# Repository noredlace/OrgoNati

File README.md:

# OrgoNati

A design by u/lizardsticks

A an ergonomic ortholinear angled board. Inspiration from the atreus with a twist on the modifiers and keys to fit most keycap designs. <br /> 

Nonstandard keycaps include the 2.25u Novelty on the left side. This keycap is meant to be used with either the Enter Key or a Novelty Enter Key. This allows a symmetrical design.

The left shift key was chosen to be a 2.75u with the right shift being a split shift 1.75u + 1u key.

Schematic was done in a 9 x 8 layout. This is due to the 66 keys on the OrgoNati. Limitations of the ProMicro's PinOuts means the tracing is messy due to the odd path of each switch/diode. <br />

The glory of ugly tracing can be seen

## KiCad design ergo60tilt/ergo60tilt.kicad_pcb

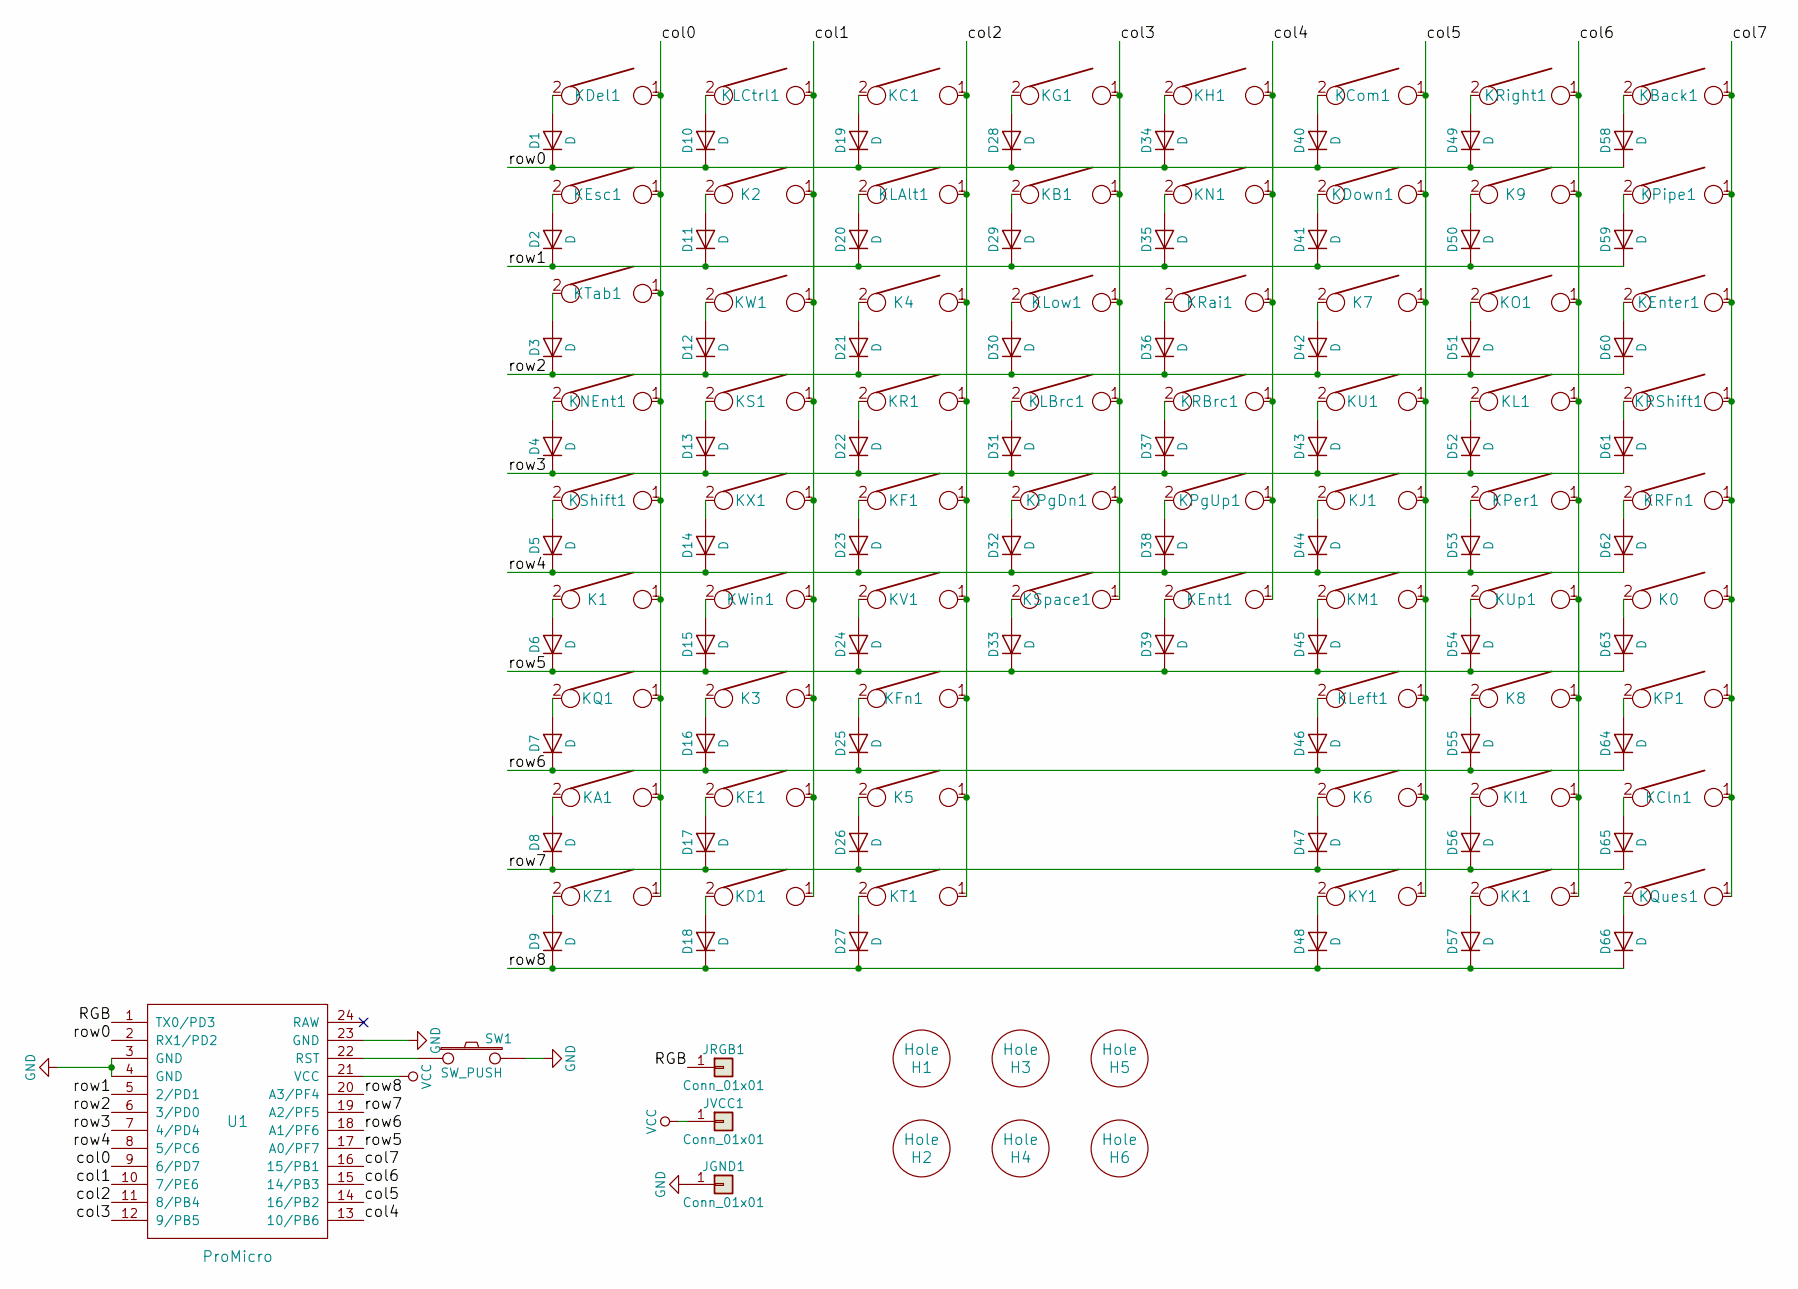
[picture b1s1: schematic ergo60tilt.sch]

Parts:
D1, D2, D3, D4, D5, D6, D7, D8, D9, D10, D11, D12, D13, D14, D15, D16, D17, D18, D19, D20, D21, D22, D23, D24, D25, D26, D27, D28, D29, D30, D31, D32, D33, D34, D35, D36, D37, D38, D39, D40, D41, D42, D43, D44, D45, D46, D47, D48, D49, D50, D51, D52, D53, D54, D55, D56, D57, D58, D59, D60, D61, D62, D63, D64, D65, D66: D; D_SOD123_axial
H1, H2, H3, H4, H5, H6: Hole; HOLE_M2.6
JGND1: Conn_01x01; Pin_d0.9mm_L10.0mm_W2.4mm_FlatFork
JRGB1: Conn_01x01; Pin_d0.9mm_L10.0mm_W2.4mm_FlatFork
JVCC1: Conn_01x01; Pin_d0.9mm_L10.0mm_W2.4mm_FlatFork
K0, K1, K2, K3, K4, K5, K6, K7, K8, K9: KEYSW; Mx_Alps_100
KA1: KEYSW; Mx_Alps_100
KB1: KEYSW; Mx_Alps_100
KBack1: KEYSW; Mx_Alps_200
KC1: KEYSW; Mx_Alps_100
KCln1: KEYSW; Mx_Alps_100
KCom1: KEYSW; Mx_Alps_100
KD1: KEYSW; Mx_Alps_100
KDel1: KEYSW; Mx_Alps_100
KDown1: KEYSW; Mx_Alps_100
KE1: KEYSW; Mx_Alps_100
KEnt1: KEYSW; Mx_Alps_200
KEnter1: KEYSW; Mx_Alps_225
KEsc1: KEYSW; Mx_Alps_100
KF1: KEYSW; Mx_Alps_100
KFn1: KEYSW; Mx_Alps_100
KG1: KEYSW; Mx_Alps_100
KH1: KEYSW; Mx_Alps_100
KI1: KEYSW; Mx_Alps_100
KJ1: KEYSW; Mx_Alps_100
KK1: KEYSW; Mx_Alps_100
KL1: KEYSW; Mx_Alps_100
KLAlt1: KEYSW; Mx_Alps_100
KLBrc1: KEYSW; Mx_Alps_100
KLCtrl1: KEYSW; Mx_Alps_100
KLeft1: KEYSW; Mx_Alps_100
KLow1: KEYSW; Mx_Alps_100
KM1: KEYSW; Mx_Alps_100
KN1: KEYSW; Mx_Alps_100
KNEnt1: KEYSW; Mx_Alps_225
KO1: KEYSW; Mx_Alps_100
KP1: KEYSW; Mx_Alps_100
KPer1: KEYSW; Mx_Alps_100
KPgDn1: KEYSW; Mx_Alps_100
KPgUp1: KEYSW; Mx_Alps_100
KPipe1: KEYSW; Mx_Alps_150
KQ1: KEYSW; Mx_Alps_100
KQues1: KEYSW; Mx_Alps_100
KR1: KEYSW; Mx_Alps_100
KRBrc1: KEYSW; Mx_Alps_100
KRFn1: KEYSW; Mx_Alps_100
KRShift1: KEYSW; Mx_Alps_175
KRai1: KEYSW; Mx_Alps_100
KRight1: KEYSW; Mx_Alps_100
KS1: KEYSW; Mx_Alps_100
KShift1: KEYSW; Mx_Alps_275
KSpace1: KEYSW; Mx_Alps_200
KT1: KEYSW; Mx_Alps_100
KTab1: KEYSW; Mx_Alps_150
KU1: KEYSW; Mx_Alps_100
KUp1: KEYSW; Mx_Alps_100
KV1: KEYSW; Mx_Alps_100
KW1: KEYSW; Mx_Alps_100
KWin1: KEYSW; Mx_Alps_100
KX1: KEYSW; Mx_Alps_100
KY1: KEYSW; Mx_Alps_100
KZ1: KEYSW; Mx_Alps_100
SW1: SW_PUSH; SW_SPST_TL3342
U1: ProMicro; Pro_Micro

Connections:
/RGB: JRGB1.1, U1.1 (TX0/PD3)
/col0: K1.1, KA1.1, KDel1.1, KEsc1.1, KNEnt1.1, KQ1.1, KShift1.1, KTab1.1, KZ1.1, U1.9 (6/PD7)
/col1: K2.1, K3.1, KD1.1, KE1.1, KLCtrl1.1, KS1.1, KW1.1, KWin1.1, KX1.1, U1.10 (7/PE6)
/col2: K4.1, K5.1, KC1.1, KF1.1, KFn1.1, KLAlt1.1, KR1.1, KT1.1, KV1.1, U1.11 (8/PB4)
/col3: KB1.1, KG1.1, KLBrc1.1, KLow1.1, KPgDn1.1, KSpace1.1, U1.12 (9/PB5)
/col4: KEnt1.1, KH1.1, KN1.1, KPgUp1.1, KRBrc1.1, KRai1.1, U1.13 (10/PB6)
/col5: K6.1, K7.1, KCom1.1, KDown1.1, KJ1.1, KLeft1.1, KM1.1, KU1.1, KY1.1, U1.14 (16/PB2)
/col6: K8.1, K9.1, KI1.1, KK1.1, KL1.1, KO1.1, KPer1.1, KRight1.1, KUp1.1, U1.15 (14/PB3)
/col7: K0.1, KBack1.1, KCln1.1, KEnter1.1, KP1.1, KPipe1.1, KQues1.1, KRFn1.1, KRShift1.1, U1.16 (15/PB1)
/row0: D1.1 (K), D10.1 (K), D19.1 (K), D28.1 (K), D34.1 (K), D40.1 (K), D49.1 (K), D58.1 (K), U1.2 (RX1/PD2)
/row1: D2.1 (K), D11.1 (K), D20.1 (K), D29.1 (K), D35.1 (K), D41.1 (K), D50.1 (K), D59.1 (K), U1.5 (2/PD1)
/row2: D3.1 (K), D12.1 (K), D21.1 (K), D30.1 (K), D36.1 (K), D42.1 (K), D51.1 (K), D60.1 (K), U1.6 (3/PD0)
/row3: D4.1 (K), D13.1 (K), D22.1 (K), D31.1 (K), D37.1 (K), D43.1 (K), D52.1 (K), D61.1 (K), U1.7 (4/PD4)
/row4: D5.1 (K), D14.1 (K), D23.1 (K), D32.1 (K), D38.1 (K), D44.1 (K), D53.1 (K), D62.1 (K), U1.8 (5/PC6)
/row5: D6.1 (K), D15.1 (K), D24.1 (K), D33.1 (K), D39.1 (K), D45.1 (K), D54.1 (K), D63.1 (K), U1.17 (A0/PF7)
/row6: D7.1 (K), D16.1 (K), D25.1 (K), D46.1 (K), D55.1 (K), D64.1 (K), U1.18 (A1/PF6)
/row7: D8.1 (K), D17.1 (K), D26.1 (K), D47.1 (K), D56.1 (K), D65.1 (K), U1.19 (A2/PF5)
/row8: D9.1 (K), D18.1 (K), D27.1 (K), D48.1 (K), D57.1 (K), D66.1 (K), U1.20 (A3/PF4)
GND: JGND1.1, SW1.2, U1.3 (GND), U1.4 (GND), U1.23 (GND)
unnamed: D1.2 (A), KDel1.2
unnamed: D2.2 (A), KEsc1.2
unnamed: D3.2 (A), KTab1.2
unnamed: D4.2 (A), KNEnt1.2
unnamed: D5.2 (A), KShift1.2
unnamed: D6.2 (A), K1.2
unnamed: D7.2 (A), KQ1.2
unnamed: D8.2 (A), KA1.2
unnamed: D9.2 (A), KZ1.2
unnamed: D10.2 (A), KLCtrl1.2
unnamed: D11.2 (A), K2.2
unnamed: D12.2 (A), KW1.2
unnamed: D13.2 (A), KS1.2
unnamed: D14.2 (A), KX1.2
unnamed: D15.2 (A), KWin1.2
unnamed: D16.2 (A), K3.2
unnamed: D17.2 (A), KE1.2
unnamed: D18.2 (A), KD1.2
unnamed: D19.2 (A), KC1.2
unnamed: D20.2 (A), KLAlt1.2
unnamed: D21.2 (A), K4.2
unnamed: D22.2 (A), KR1.2
unnamed: D23.2 (A), KF1.2
unnamed: D24.2 (A), KV1.2
unnamed: D25.2 (A), KFn1.2
unnamed: D26.2 (A), K5.2
unnamed: D27.2 (A), KT1.2
unnamed: D28.2 (A), KG1.2
unnamed: D29.2 (A), KB1.2
unnamed: D30.2 (A), KLow1.2
unnamed: D31.2 (A), KLBrc1.2
unnamed: D32.2 (A), KPgDn1.2
unnamed: D33.2 (A), KSpace1.2
unnamed: D34.2 (A), KH1.2
unnamed: D35.2 (A), KN1.2
unnamed: D36.2 (A), KRai1.2
unnamed: D37.2 (A), KRBrc1.2
unnamed: D38.2 (A), KPgUp1.2
unnamed: D39.2 (A), KEnt1.2
unnamed: D40.2 (A), KCom1.2
unnamed: D41.2 (A), KDown1.2
unnamed: D42.2 (A), K7.2
unnamed: D43.2 (A), KU1.2
unnamed: D44.2 (A), KJ1.2
unnamed: D45.2 (A), KM1.2
unnamed: D46.2 (A), KLeft1.2
unnamed: D47.2 (A), K6.2
unnamed: D48.2 (A), KY1.2
unnamed: D49.2 (A), KRight1.2
unnamed: D50.2 (A), K9.2
unnamed: D51.2 (A), KO1.2
unnamed: D52.2 (A), KL1.2
unnamed: D53.2 (A), KPer1.2
unnamed: D54.2 (A), KUp1.2
unnamed: D55.2 (A), K8.2
unnamed: D56.2 (A), KI1.2
unnamed: D57.2 (A), KK1.2
unnamed: D58.2 (A), KBack1.2
unnamed: D59.2 (A), KPipe1.2
unnamed: D60.2 (A), KEnter1.2
unnamed: D61.2 (A), KRShift1.2
unnamed: D62.2 (A), KRFn1.2
unnamed: D63.2 (A), K0.2
unnamed: D64.2 (A), KP1.2
unnamed: D65.2 (A), KCln1.2
unnamed: D66.2 (A), KQues1.2
unnamed: SW1.1, U1.22 (RST)
VCC: JVCC1.1, U1.21 (VCC)

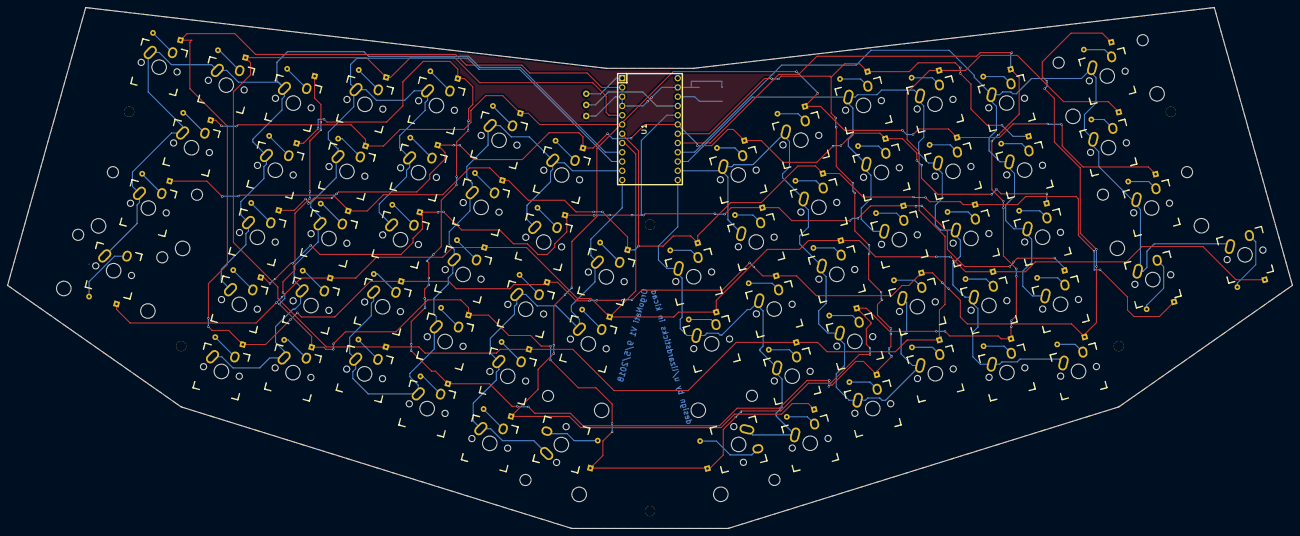
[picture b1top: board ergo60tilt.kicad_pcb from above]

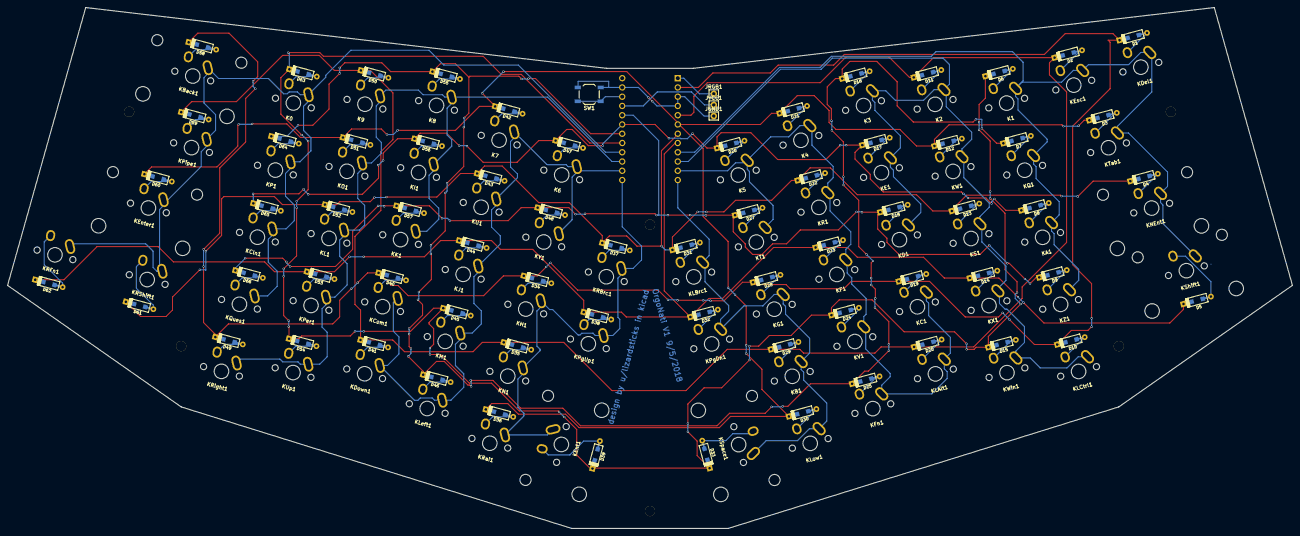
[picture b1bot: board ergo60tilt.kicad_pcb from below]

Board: 2 copper layers, 352.4 x 142.9 mm, 143 parts (70 on the bottom side), 87 nets.

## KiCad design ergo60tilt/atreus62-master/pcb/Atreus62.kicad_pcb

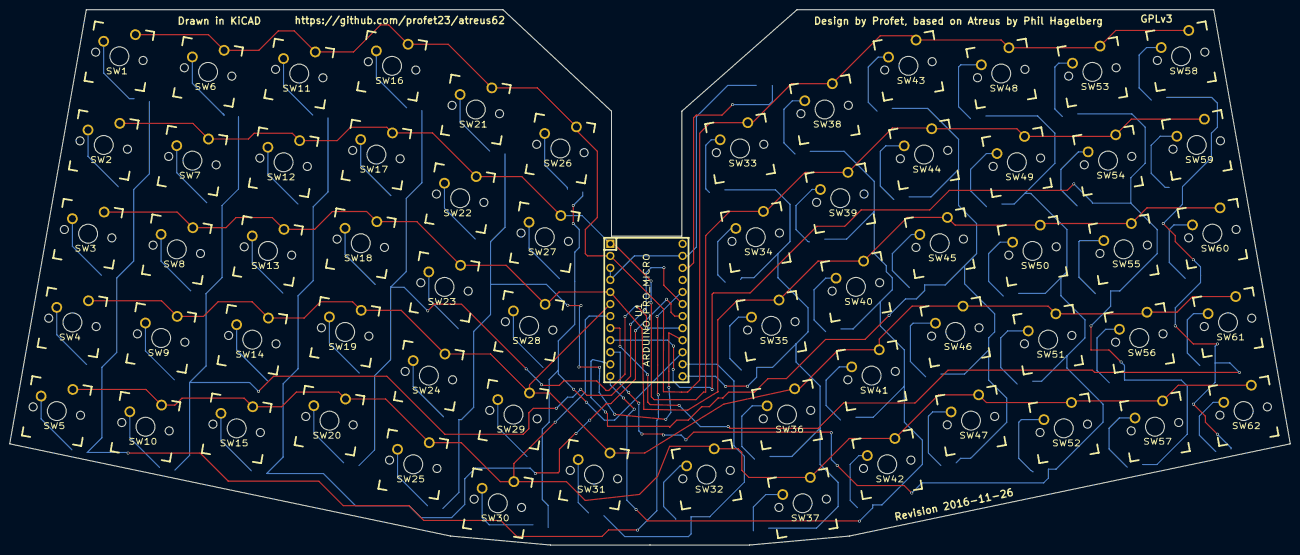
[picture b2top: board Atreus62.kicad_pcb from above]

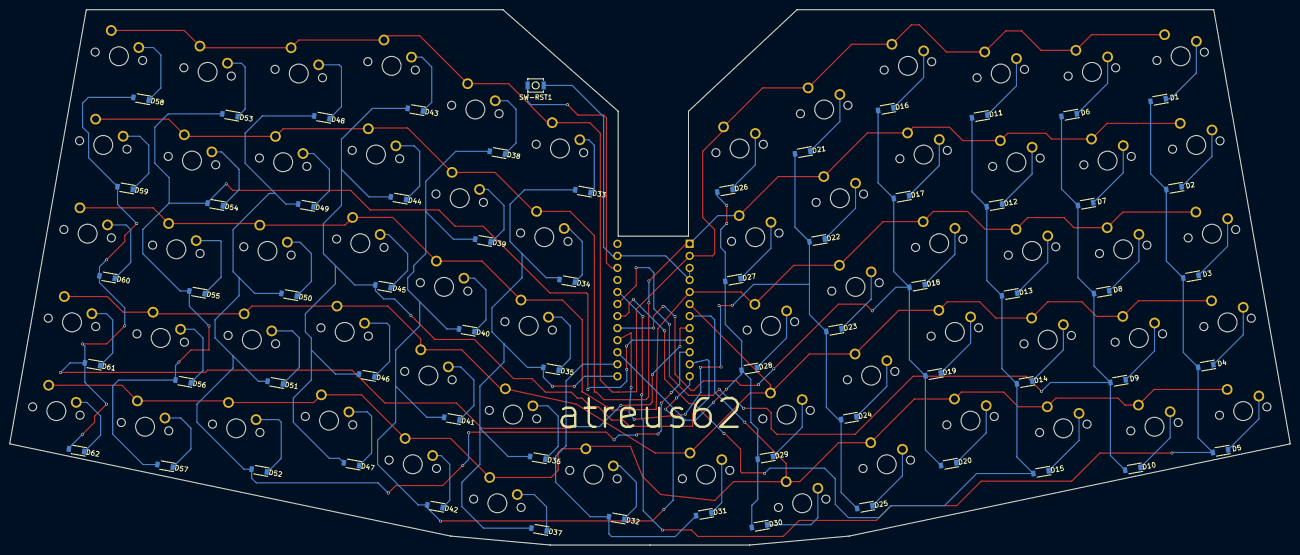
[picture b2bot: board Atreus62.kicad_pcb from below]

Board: 2 copper layers, 270.1 x 112.9 mm, 126 parts (62 on the bottom side), 82 nets.

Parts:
D1, D2, D3, D4, D5, D6, D7, D8, D9, D10, D11, D12, D13, D14, D15, D16, D17, D18, D19, D20, D21, D22, D23, D24, D25, D26, D27, D28, D29, D30, D31, D32, D33, D34, D35, D36, D37, D38, D39, D40, D41, D42, D43, D44, D45, D46, D47, D48, D49, D50, D51, D52, D53, D54, D55, D56, D57, D58, D59, D60, D61, D62: DIODE; SOD-123
SW1, SW2, SW3, SW4, SW5, SW6, SW7, SW8, SW9, SW10, SW11, SW12, SW13, SW14, SW15, SW16, SW17, SW18, SW19, SW20, SW21, SW22, SW23, SW24, SW25, SW26, SW27, SW28, SW29, SW30, SW31, SW32, SW33, SW34, SW35, SW36, SW37, SW38, SW39, SW40, SW41, SW42, SW43, SW44, SW45, SW46, SW47, SW48, SW49, SW50, SW51, SW52, SW53, SW54, SW55, SW56, SW57, SW58, SW59, SW60, SW61, SW62: SWITCH_PUSH; CHERRY_PCB_100H
SW-RST1: SWITCH_PUSH; SW_SPST_B3U-1000P
U1: ARDUINO_PRO_MICRO

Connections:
/COL0: D1.2, D2.2, D3.2, D4.2, D5.2, U1.20
/COL1: D6.2, D7.2, D8.2, D9.2, D10.2, U1.19
/COL2: D11.2, D12.2, D13.2, D14.2, D15.2, U1.18
/COL3: D16.2, D17.2, D18.2, D19.2, D20.2, U1.17
/COL4: D21.2, D22.2, D23.2, D24.2, D25.2, U1.16
/COL5: D26.2, D27.2, D28.2, D29.2, D30.2, U1.15
/COL6: D31.2, D32.2, U1.14
/COL7: D33.2, D34.2, D35.2, D36.2, D37.2, U1.13
/COL8: D38.2, D39.2, D40.2, D41.2, D42.2, U1.12
/COL9: D43.2, D44.2, D45.2, D46.2, D47.2, U1.11
/COL10: D48.2, D49.2, D50.2, D51.2, D52.2, U1.10
/COL11: D53.2, D54.2, D55.2, D56.2, D57.2, U1.9
/COL12: D58.2, D59.2, D60.2, D61.2, D62.2, U1.8
/ROW0: SW5.1, SW10.1, SW15.1, SW20.1, SW25.1, SW30.1, SW32.1, SW37.1, SW42.1, SW47.1, SW52.1, SW57.1, SW62.1, U1.7
/ROW1: SW4.1, SW9.1, SW14.1, SW19.1, SW24.1, SW29.1, SW31.1, SW36.1, SW41.1, SW46.1, SW51.1, SW56.1, SW61.1, U1.6
/ROW2: SW3.1, SW8.1, SW13.1, SW18.1, SW23.1, SW28.1, SW35.1, SW40.1, SW45.1, SW50.1, SW55.1, SW60.1, U1.5
/ROW3: SW2.1, SW7.1, SW12.1, SW17.1, SW22.1, SW27.1, SW34.1, SW39.1, SW44.1, SW49.1, SW54.1, SW59.1, U1.1
/ROW4: SW1.1, SW6.1, SW11.1, SW16.1, SW21.1, SW26.1, SW33.1, SW38.1, SW43.1, SW48.1, SW53.1, SW58.1, U1.2
GND: SW-RST1.1, U1.3, U1.4, U1.23
unnamed: D1.1, SW1.2
unnamed: D2.1, SW2.2
unnamed: D3.1, SW3.2
unnamed: D4.1, SW4.2
unnamed: D5.1, SW5.2
unnamed: D6.1, SW6.2
unnamed: D7.1, SW7.2
unnamed: D8.1, SW8.2
unnamed: D9.1, SW9.2
unnamed: D10.1, SW10.2
unnamed: D11.1, SW11.2
unnamed: D12.1, SW12.2
unnamed: D13.1, SW13.2
unnamed: D14.1, SW14.2
unnamed: D15.1, SW15.2
unnamed: D16.1, SW16.2
unnamed: D17.1, SW17.2
unnamed: D18.1, SW18.2
unnamed: D19.1, SW19.2
unnamed: D20.1, SW20.2
unnamed: D21.1, SW21.2
unnamed: D22.1, SW22.2
unnamed: D23.1, SW23.2
unnamed: D24.1, SW24.2
unnamed: D25.1, SW25.2
unnamed: D26.1, SW26.2
unnamed: D27.1, SW27.2
unnamed: D28.1, SW28.2
unnamed: D29.1, SW29.2
unnamed: D30.1, SW30.2
unnamed: D31.1, SW31.2
unnamed: D32.1, SW32.2
unnamed: D33.1, SW33.2
unnamed: D34.1, SW34.2
unnamed: D35.1, SW35.2
unnamed: D36.1, SW36.2
unnamed: D37.1, SW37.2
unnamed: D38.1, SW38.2
unnamed: D39.1, SW39.2
unnamed: D40.1, SW40.2
unnamed: D41.1, SW41.2
unnamed: D42.1, SW42.2
unnamed: D43.1, SW43.2
unnamed: D44.1, SW44.2
unnamed: D45.1, SW45.2
unnamed: D46.1, SW46.2
unnamed: D47.1, SW47.2
unnamed: D48.1, SW48.2
unnamed: D49.1, SW49.2
unnamed: D50.1, SW50.2
unnamed: D51.1, SW51.2
unnamed: D52.1, SW52.2
unnamed: D53.1, SW53.2
unnamed: D54.1, SW54.2
unnamed: D55.1, SW55.2
unnamed: D56.1, SW56.2
unnamed: D57.1, SW57.2
unnamed: D58.1, SW58.2
unnamed: D59.1, SW59.2
unnamed: D60.1, SW60.2
unnamed: D61.1, SW61.2
unnamed: D62.1, SW62.2
unnamed: SW-RST1.2, U1.22

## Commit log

2018-09-06 push orgonati
2018-09-06 push rotated pcb
2018-09-06 push completed orgonati. update readme
2018-09-06 update save
2018-09-06 add revisions to matrix layout in kle
2019-06-12 update?
    dont really know what this update brings lol

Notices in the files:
ergo60tilt/atreus62-master/pcb/Atreus62.kicad_pcb:
GPLv3
